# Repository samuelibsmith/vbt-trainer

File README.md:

# VBT Trainer

A DIY velocity-based training (VBT) device that measures barbell speed in real time. A spring-loaded spool with a 600 PPR rotary encoder measures bar displacement, and an ESP32 turns that into velocity, rep metrics, an on-device display, BLE output, and CSV logs.

## What it does

- Measures barbell velocity (±2% accuracy target) using a spring-loaded

  spool and 600 PPR rotary encoder

- Streams live velocity data over BLE to a phone app

- Logs session data to CSV for analysis

- Computes: MCV, peak velocity, velocity loss %, estimated 1RM, (using weight lifted: peak power, avg power)

## Hardware

| Microcontroller | ESP32 DevKit v1 | $9 | 

| Encoder | Taiss 600PPR | $18 | 

| Display | SSD1306 0.96" OLED | $3 |

| Battery | Samsung 30Q 18650 3000mAh 15A Battery | $4 |

| Battery Holder | Samsung 30Q 18650 3000mAh 15A Battery | $10 |

Full list: [`hardware/v_1_bom.csv`](hardware/v_1_bom.csv)

## Wiring

| Signal | ESP32 pin | Notes |
|--------|-----------|-------|
| Encoder channel A | GPIO 18 | 10 kOhm pull-up to 3.3 V |
| Encoder channel B | GPIO 19 | 10 kOhm pull-up to 3.3 V |
| OLED SDA | GPIO 21 | I2C address 0x3C |
| OLED SCL | GPIO 22 | |
| Reset button | GPIO 4 | <!-- TODO: to GND with internal pull-up? confirm from main.cpp --> |
| Battery + | Vin | also powers the encoder directly |

Pins are defined in [`firmware/include/config.h`](firmware/include/config.h). Wiring notes: [`docs/wiring_diagram.md`](docs/wiring_diagram.md).

> **Power warning:** the current design connects a bare 18650 directly to Vin with no protection circuit or charger. Use a protected cell or a charger/protection module, and never leave the cell unattended while charging. Expect voltage sag (and possible brownouts) as the cell nears empty.

## Getting started

### 1. Build the hardware
1a. Circuitry
Wire everything per the table above. Measure your own spool's effective diameter, because it sets the mm-per-count scale for every reading.
1b. 3D-Printed Housing
Unless you use the exact same tape measure internals from a (Ace 12 ft. L X 3/4 in. W Compact Tape Measure 1 pk), you will need to redesign both the key that translates torque from the spool to the encoder, and the spacing of encoder and the spool. The 3D model of the spool is a 3D replica of the actual spool, with the same measurements. If you order the same spool, the 3D-printed housing is good to go as is. 

### 2. Flash the firmware
Requirements: VS Code with the PlatformIO extension (or the `pio` CLI).

1. Open the `firmware/` folder in PlatformIO. Libraries install automatically from `platformio.ini`.
2. Set `SPOOL_DIAMETER_MM` in `firmware/include/config.h` to your measured spool diameter (the repo default is 37.47).
3. Build and upload: `pio run -t upload`
4. Open the serial monitor at 115200 baud to confirm output: `pio device monitor`

Key settings in `config.h`:

| Setting | Default | Meaning |
|---------|---------|---------|
| `SAMPLE_RATE_HZ` | 200 | velocity calculation rate |
| `SMOOTHING_WINDOW` | 5 | moving-average length (samples) |
| `REP_START_VELOCITY` | 0.08 m/s | rep begins above this |
| `REP_END_VELOCITY` | 0.05 m/s | rep ends below this |
| `REP_MIN_DURATION_MS` | 150 | ignore shorter spikes |
| `BLE_BROADCAST_HZ` | 10 | BLE update rate |

### 3. Log data
Requires Python 3.9-3.12 (the pinned numpy 1.26 has no wheels for 3.13).

```bash
python -m venv .venv
source .venv/bin/activate        # Windows: .venv\Scripts\activate
pip install -r python/requirements.txt

python python/serial_logger.py

## Build Log

- [X] Phase 1: Sensor validation

- [ ] Phase 2: Firmware + Python pipeline

- [ ] Phase 3: Housing design and fabrication

- [ ] Phase 4: Phone app + dashboard

## License

MIT - see [LICENSE](LICENSE).

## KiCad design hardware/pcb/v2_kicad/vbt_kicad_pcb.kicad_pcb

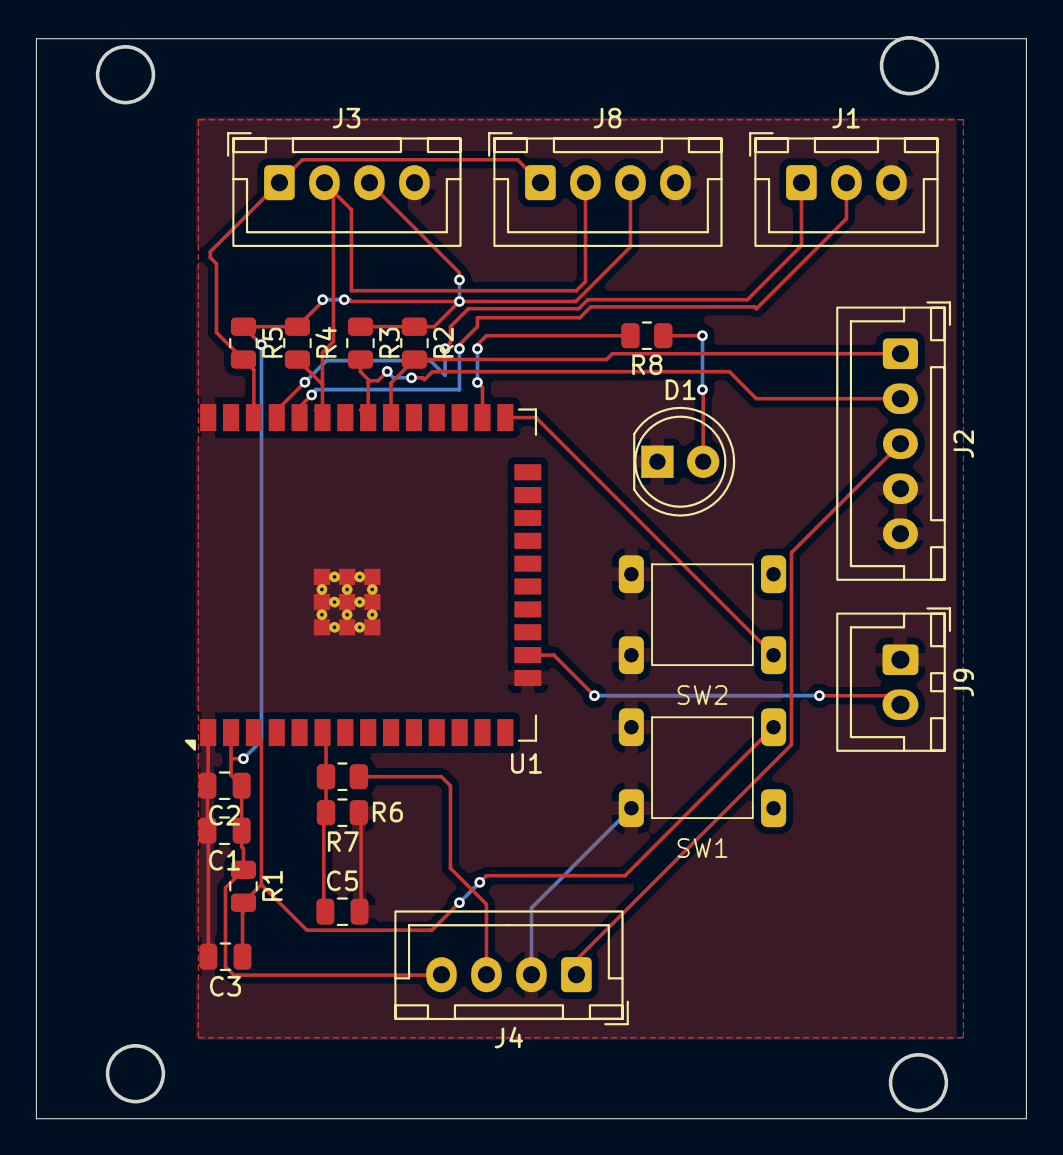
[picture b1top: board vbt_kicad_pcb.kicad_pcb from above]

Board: 2 copper layers, 55.0 x 60.0 mm, 22 parts (0 on the bottom side), 16 nets.

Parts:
C1: 10 µF; C_0805_2012Metric
C2: 100 nF; C_0805_2012Metric
C3: 1 µF; C_0805_2012Metric
C5: 100nF; C_0805_2012Metric
D1: LED; LED_D5.0mm
J1: Serial Connector; JST_XH_B3B-XH-A_1x03_P2.50mm_Vertical
J2: Rotary Encoder; JST_XH_B5B-XH-A_1x05_P2.50mm_Vertical
J3: I2C Display; JST_XH_B4B-XH-A_1x04_P2.50mm_Vertical
J4: Power Connector; JST_XH_B4B-XH-A_1x04_P2.50mm_Vertical
J8: I2C Magnet Sensor; JST_XH_B4B-XH-A_1x04_P2.50mm_Vertical
J9: Rep Reset Button; JST_XH_B2B-XH-A_1x02_P2.50mm_Vertical
R1, R2, R3: 10k; R_0805_2012Metric
R4, R5: 4.7k; R_0805_2012Metric
R6, R7: 100k; R_0805_2012Metric
R8: 330Ω; R_0805_2012Metric
SW1, SW2: SW_Push; SW_Tactile_SCHURTER_LSH_6x6mm
U1: ESP32-WROOM-32E

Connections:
+3V3: C1.1, C2.1, J3.3, J4.4, J8.3, R1.1, R2.1, R3.1, R4.1, R5.1, U1.2 (VDD)
/+5V: J2.3, J4.1
/ENC_A: J2.1, R2.2, U1.30 (IO18)
/ENC_B: J2.2, R3.2, U1.31 (IO19)
/ESP_RX: J1.2, U1.34 (RXD0/IO3)
/ESP_TX: J1.1, U1.35 (TXD0/IO1)
/I2C_SCL: J3.1, J8.1, R5.2, U1.36 (IO22)
/I2C_SDA: J3.2, J8.2, R4.2, U1.33 (IO21)
/VBAT_SENSE: C5.1, R6.2, R7.2, U1.6 (IO34)
GND: C1.2, C2.2, C3.2, C5.2, D1.1 (K), J1.3, J2.4, J2.5, J3.4, J4.2, J8.4, J9.1, R7.1, SW1.1, SW2.1, U1.1 (GND), U1.15 (GND), U1.38 (GND), U1.39 (GND)
unnamed: D1.2 (A), R8.1
unnamed: J9.2, U1.16 (IO13)
unnamed: C3.1, R1.2, SW1.2, U1.3 (EN)
unnamed: SW2.2, U1.25 (IO0)
unnamed: R8.2, U1.26 (IO4)
VBAT: J4.3, R6.1
